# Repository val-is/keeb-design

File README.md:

# keeb-design

repo containing various experiments and projects related to mechanical keyboard design and implementation

projecst are done using KiCad

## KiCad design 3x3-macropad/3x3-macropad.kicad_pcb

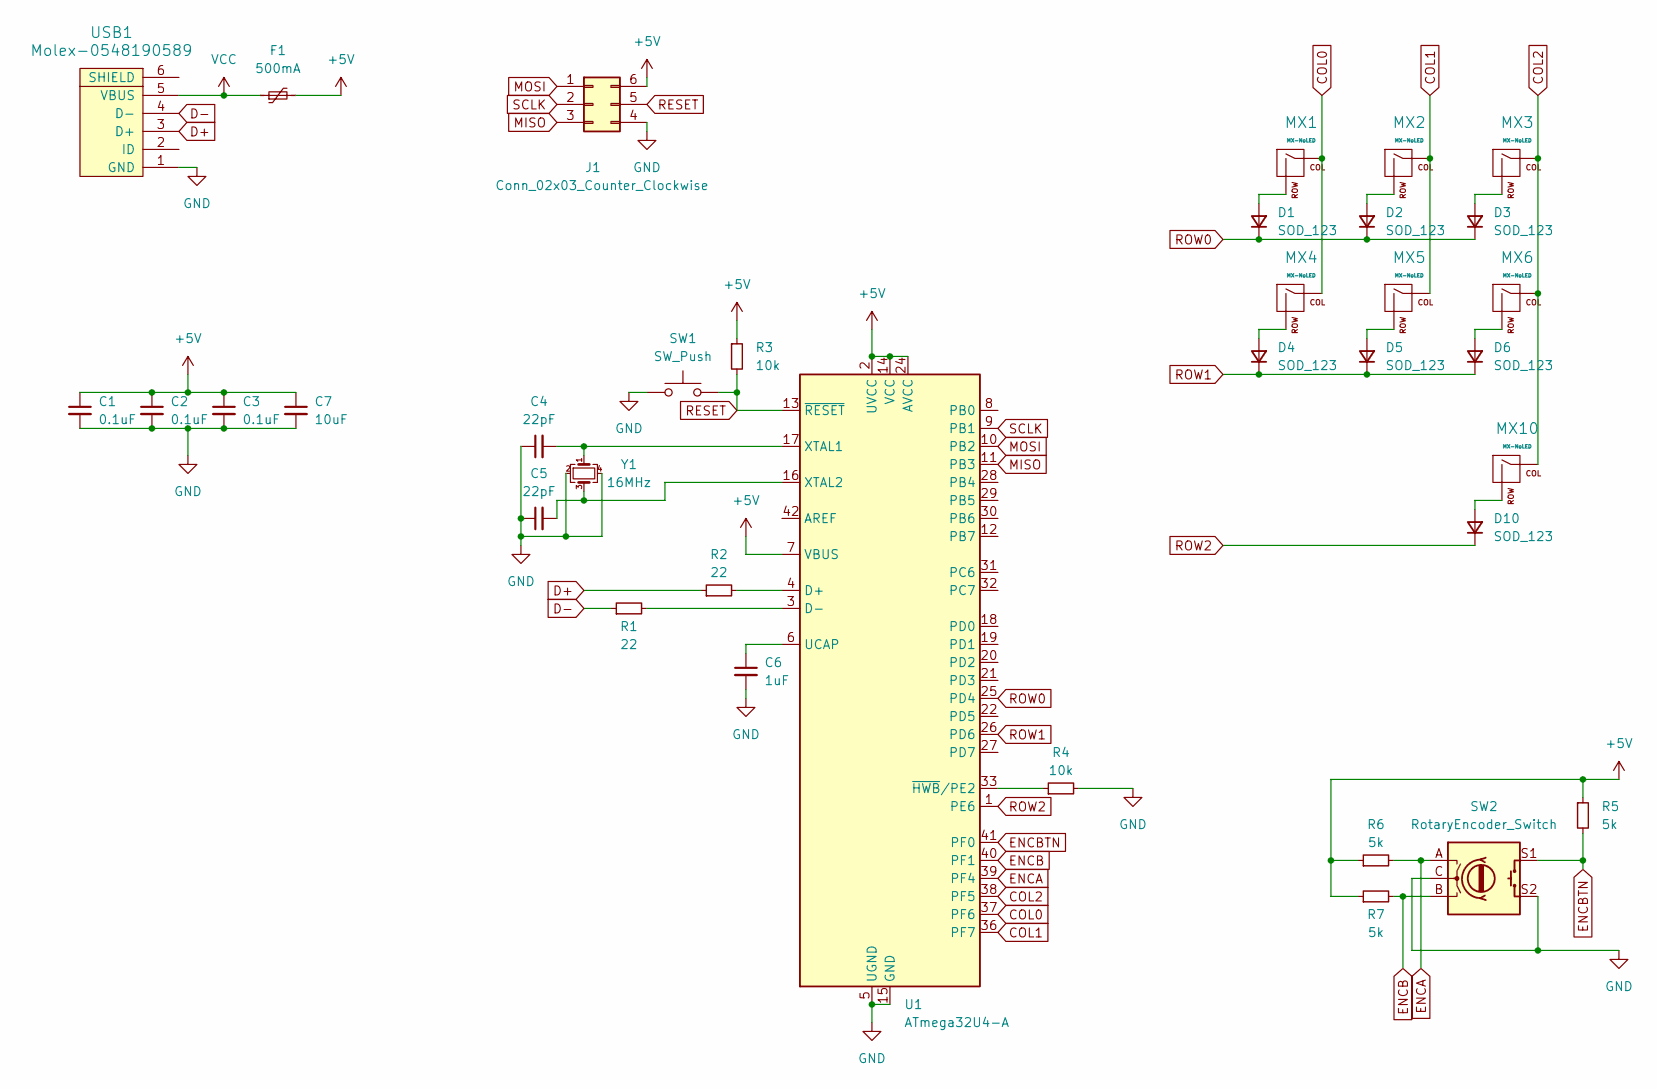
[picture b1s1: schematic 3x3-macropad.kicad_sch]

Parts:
C1, C2, C3: 0.1uF; C_0805_2012Metric
C4, C5: 22pF; C_0805_2012Metric
C6: 1uF; C_0805_2012Metric
C7: 10uF; C_0805_2012Metric
D1, D2, D3, D4, D5, D6, D10: SOD_123; D_SOD-123
F1: 500mA; Fuse_1206_3216Metric
J1: Conn_02x03_Counter_Clockwise; PinHeader_2x03_P1.27mm_Horizontal
MX1, MX2, MX3, MX4, MX5, MX6, MX10: MX-NoLED; MX-1U-NoLED
R1, R2: 22; R_0805_2012Metric
R3, R4: 10k; R_0805_2012Metric
R5, R6, R7: 5k; R_0805_2012Metric
SW1: SW_Push; SKQG-1155865
SW2: RotaryEncoder_Switch; RotaryEncoder_Alps_EC11E-Switch_Vertical_H20mm
U1: ATmega32U4-A; TQFP-44_10x10mm_P0.8mm
USB1: Molex-0548190589
Y1: 16MHz; Crystal_SMD_3225-4Pin_3.2x2.5mm

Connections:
+5V: C1.1, C2.1, C3.1, C7.1, F1.2, J1.6, R3.1, R5.1, R6.1, R7.1, U1.2 (UVCC), U1.7 (VBUS), U1.14 (VCC), U1.24 (AVCC), U1.34 (VCC), U1.44 (AVCC)
COL0: MX1.1 (COL), MX4.1 (COL), U1.37 (PF6)
COL1: MX2.1 (COL), MX5.1 (COL), U1.36 (PF7)
COL2: MX3.1 (COL), MX6.1 (COL), MX10.1 (COL), U1.38 (PF5)
D+: R2.1, USB1.3 (D+)
D-: R1.1, USB1.4 (D-)
ENCA: R6.2, SW2.A, U1.39 (PF4)
ENCB: R7.2, SW2.B, U1.40 (PF1)
ENCBTN: R5.2, SW2.S1, U1.41 (PF0)
GND: C1.2, C2.2, C3.2, C4.1, C5.1, C6.2, C7.2, J1.4, R4.2, SW1.1, SW2.C, SW2.S2, U1.5 (UGND), U1.15 (GND), U1.23 (GND), U1.35 (GND), U1.43 (GND), USB1.1 (GND), Y1.2, Y1.4
MISO: J1.3, U1.11 (PB3)
MOSI: J1.1, U1.10 (PB2)
unnamed: D1.2 (A), MX1.2 (ROW)
unnamed: D2.2 (A), MX2.2 (ROW)
unnamed: D3.2 (A), MX3.2 (ROW)
unnamed: D4.2 (A), MX4.2 (ROW)
unnamed: D5.2 (A), MX5.2 (ROW)
unnamed: D6.2 (A), MX6.2 (ROW)
unnamed: D10.2 (A), MX10.2 (ROW)
unnamed: R2.2, U1.4 (D+)
unnamed: R1.2, U1.3 (D-)
unnamed: C6.1, U1.6 (UCAP)
unnamed: C4.2, U1.17 (XTAL1), Y1.1
unnamed: C5.2, U1.16 (XTAL2), Y1.3
unnamed: R4.1, U1.33 (~HWB/PE2)
RESET: J1.5, R3.2, SW1.2, U1.13 (~RESET)
ROW0: D1.1 (K), D2.1 (K), D3.1 (K), U1.25 (PD4)
ROW1: D4.1 (K), D5.1 (K), D6.1 (K), U1.26 (PD6)
ROW2: D10.1 (K), U1.1 (PE6)
SCLK: J1.2, U1.9 (PB1)
VCC: F1.1, USB1.5 (VBUS)

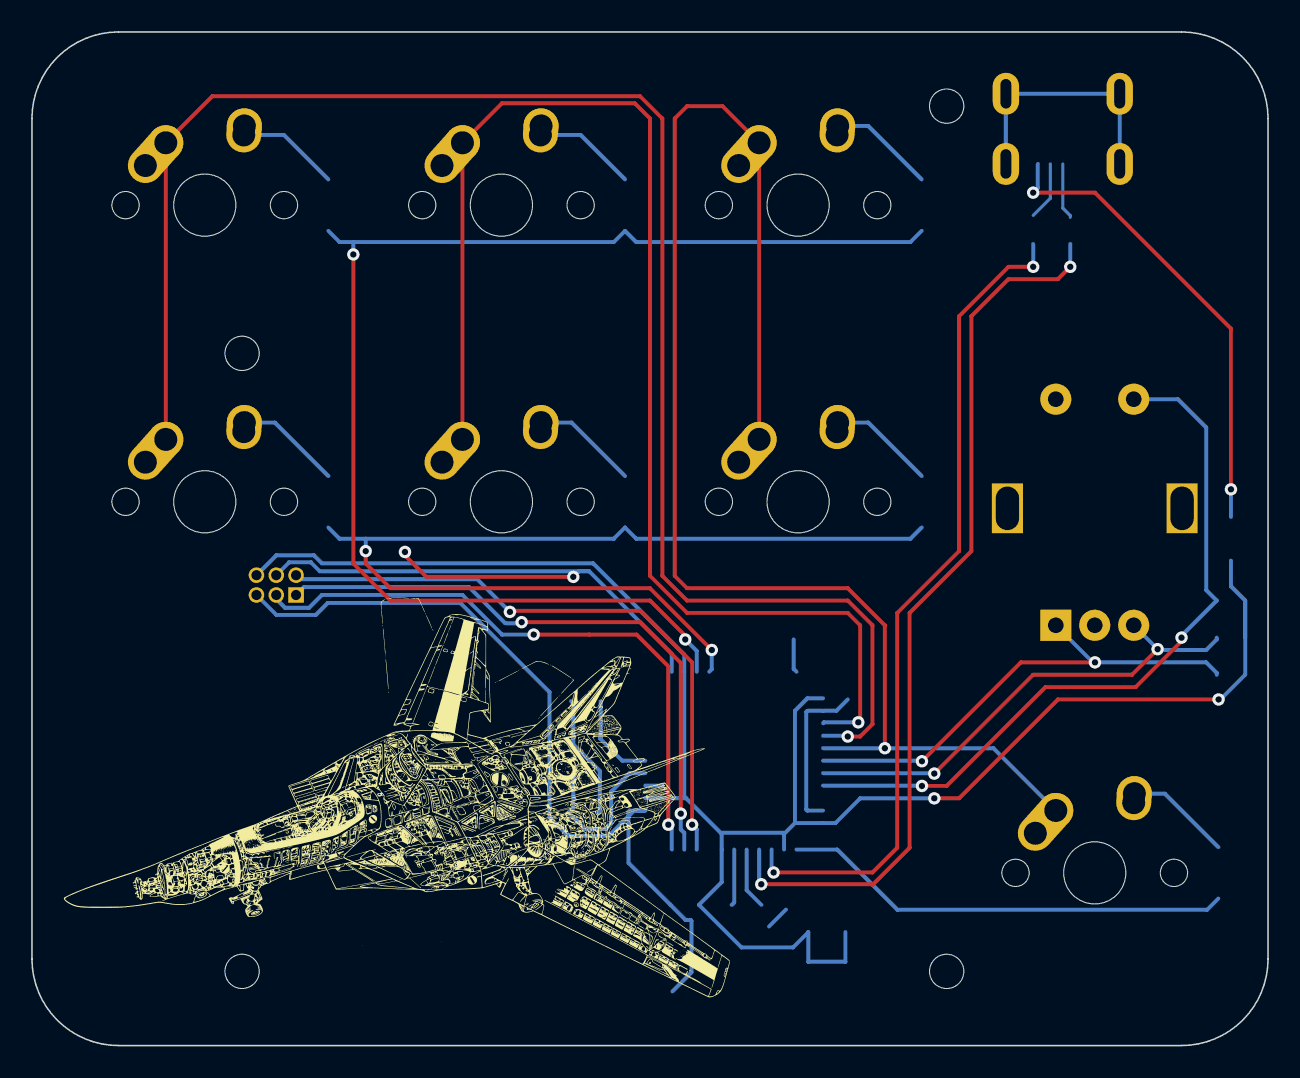
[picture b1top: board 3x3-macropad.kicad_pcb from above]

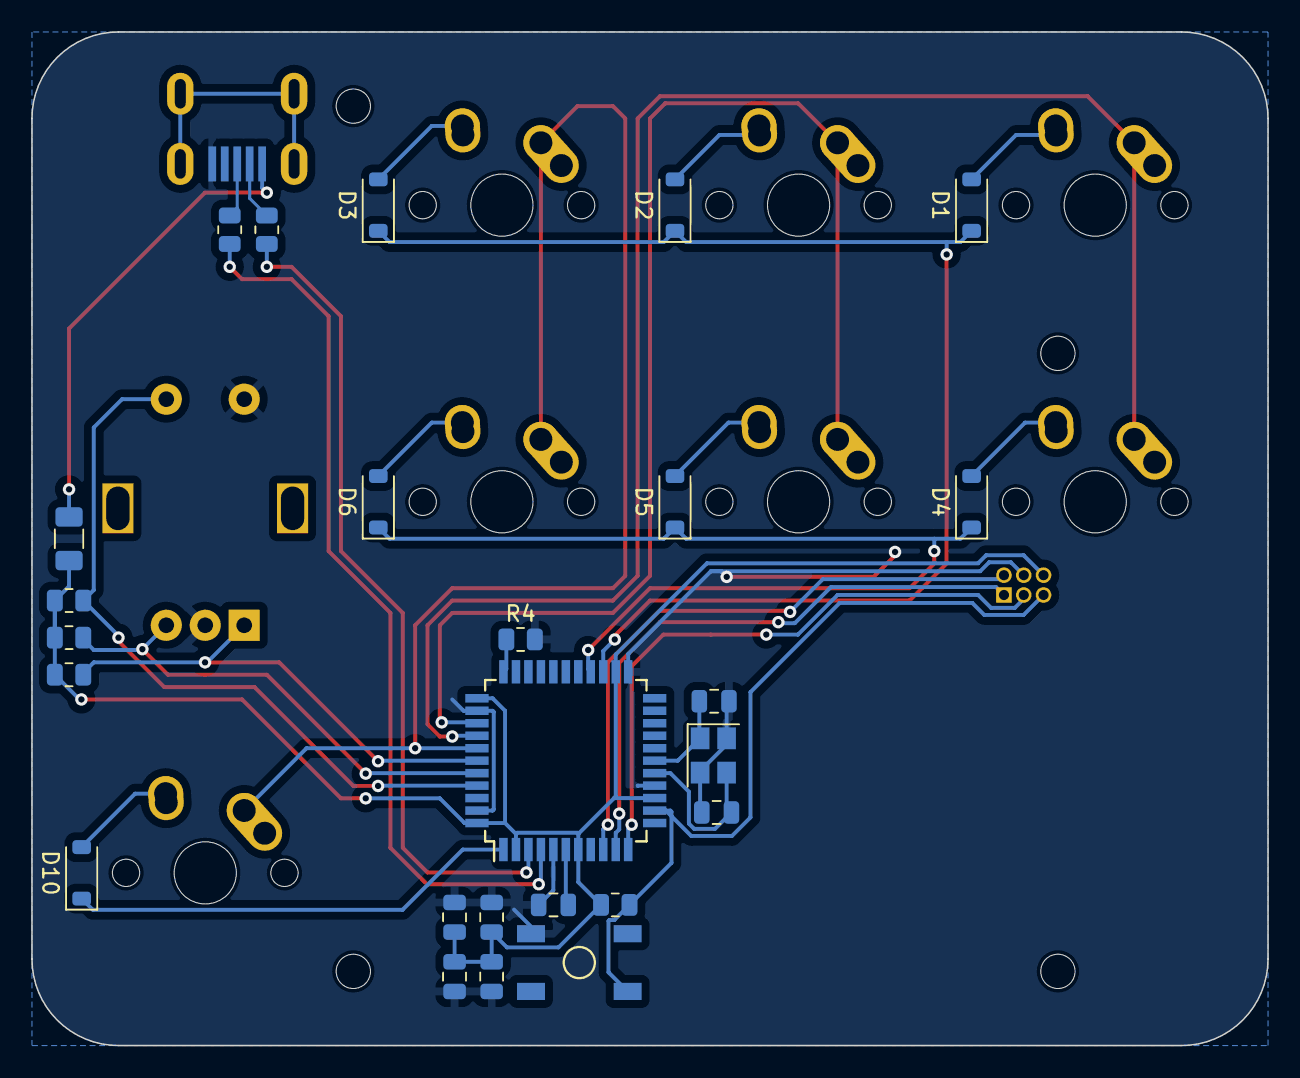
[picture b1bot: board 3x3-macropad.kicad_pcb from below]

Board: 2 copper layers, 79.3 x 65.0 mm, 35 parts (27 on the bottom side), 31 nets.

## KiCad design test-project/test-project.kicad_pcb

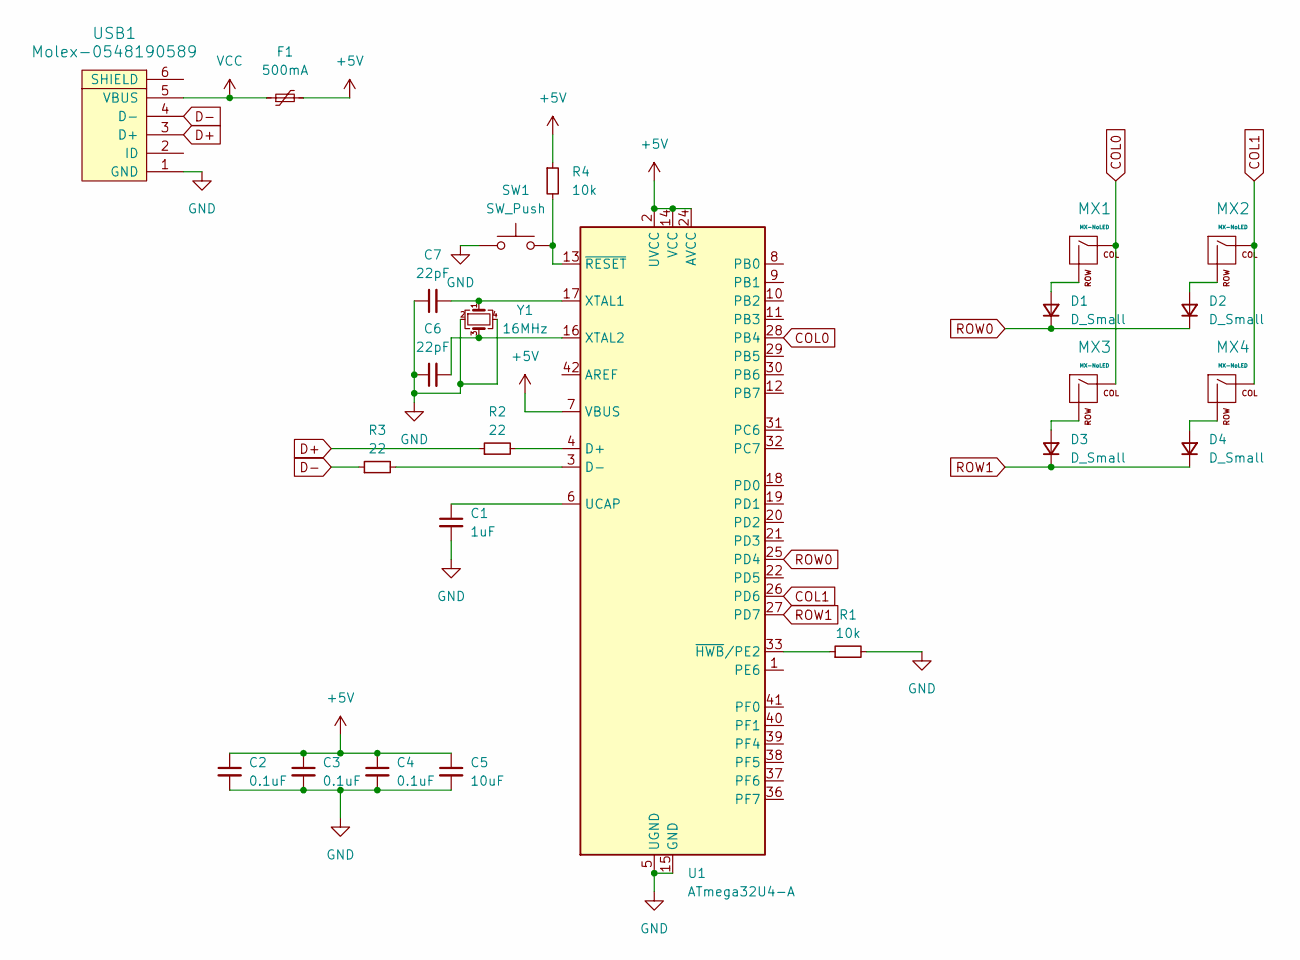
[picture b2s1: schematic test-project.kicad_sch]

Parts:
C1: 1uF; C_0805_2012Metric
C2, C3, C4: 0.1uF; C_0805_2012Metric
C5: 10uF; C_0805_2012Metric
C6, C7: 22pF; C_0805_2012Metric
D1, D2, D3, D4: D_Small; D_SOD-123
F1: 500mA; Fuse_1206_3216Metric
MX1, MX2, MX3, MX4: MX-NoLED; MX-1U-NoLED
R1, R4: 10k; R_0805_2012Metric
R2, R3: 22; R_0805_2012Metric
SW1: SW_Push; SKQG-1155865
U1: ATmega32U4-A; TQFP-44_10x10mm_P0.8mm
USB1: Molex-0548190589
Y1: 16MHz; Crystal_SMD_3225-4Pin_3.2x2.5mm

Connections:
+5V: C2.1, C3.1, C4.1, C5.1, F1.2, R4.1, U1.2 (UVCC), U1.7 (VBUS), U1.14 (VCC), U1.24 (AVCC), U1.34 (VCC), U1.44 (AVCC)
COL0: MX1.1 (COL), MX3.1 (COL), U1.28 (PB4)
COL1: MX2.1 (COL), MX4.1 (COL), U1.26 (PD6)
D+: R2.1, USB1.3 (D+)
D-: R3.1, USB1.4 (D-)
GND: C1.2, C2.2, C3.2, C4.2, C5.2, C6.1, C7.1, R1.2, SW1.1, U1.5 (UGND), U1.15 (GND), U1.23 (GND), U1.35 (GND), U1.43 (GND), USB1.1 (GND), Y1.2, Y1.4
unnamed: D1.2 (A), MX1.2 (ROW)
unnamed: D2.2 (A), MX2.2 (ROW)
unnamed: D3.2 (A), MX3.2 (ROW)
unnamed: D4.2 (A), MX4.2 (ROW)
unnamed: R2.2, U1.4 (D+)
unnamed: R3.2, U1.3 (D-)
unnamed: C1.1, U1.6 (UCAP)
unnamed: C7.2, U1.17 (XTAL1), Y1.1
unnamed: C6.2, U1.16 (XTAL2), Y1.3
unnamed: R1.1, U1.33 (~HWB/PE2)
unnamed: R4.2, SW1.2, U1.13 (~RESET)
ROW0: D1.1 (K), D2.1 (K), U1.25 (PD4)
ROW1: D3.1 (K), D4.1 (K), U1.27 (PD7)
VCC: F1.1, USB1.5 (VBUS)

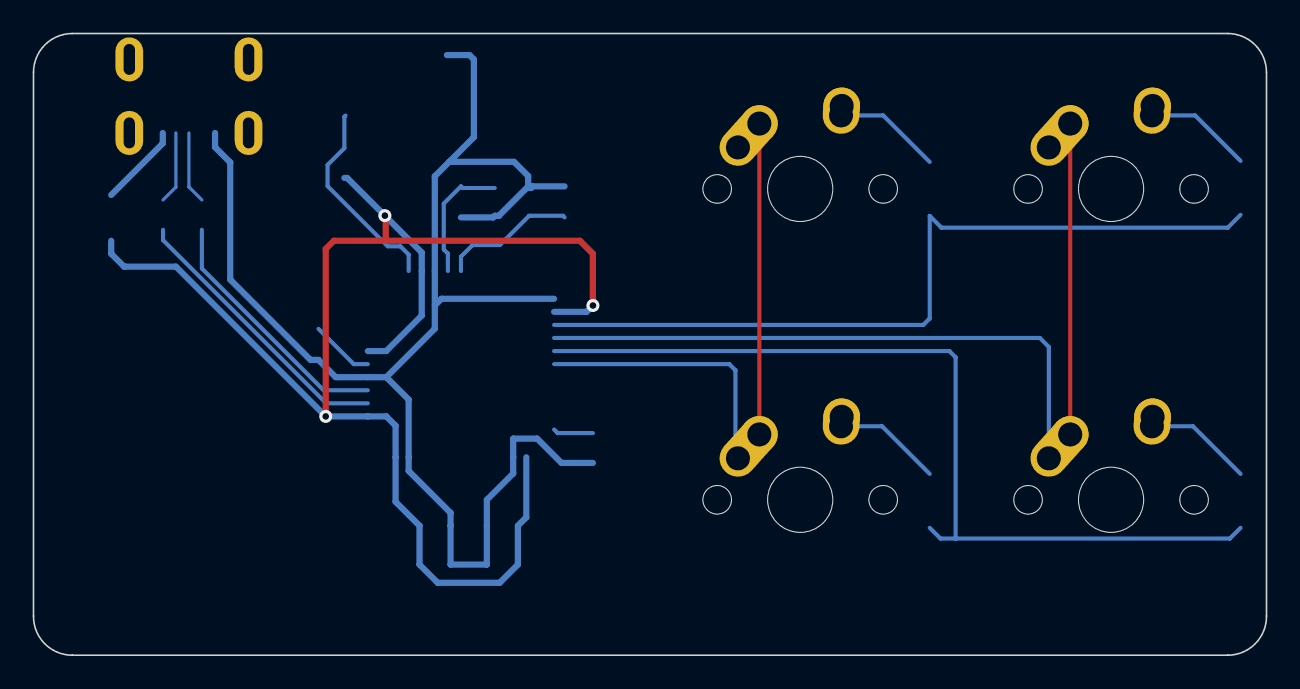
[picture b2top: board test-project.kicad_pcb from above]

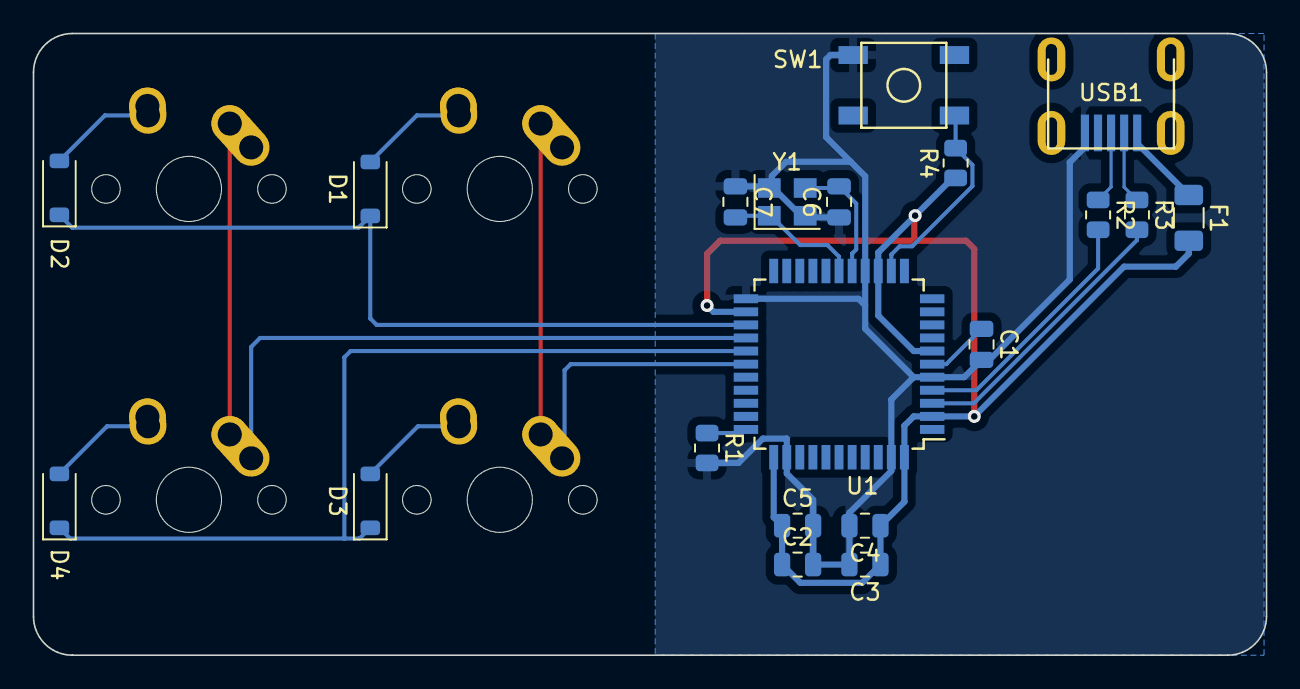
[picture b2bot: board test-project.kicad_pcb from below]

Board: 2 copper layers, 75.5 x 38.1 mm, 24 parts (20 on the bottom side), 20 nets.

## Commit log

2023-06-14 initialize project + submodules
2023-06-14 add footprint libraries
2023-06-14 routing :)
2023-06-15 roughly done with demo PCB
2023-06-15 fix library referencing
2023-06-15 make kicad project for 3x3 macropad
2023-06-15 add readme(s)
2023-06-15 start pcb layout for macropad
2023-06-18 first attempt routing 3x3
2023-06-25 redo pcb routing (better)
2023-07-10 finished routing (sans standoffs) for 3x3
2023-07-11 resized 3x3, readied for export to jlcpcb
2023-07-12 add BOM
2023-08-12 add isp flashing breakout
